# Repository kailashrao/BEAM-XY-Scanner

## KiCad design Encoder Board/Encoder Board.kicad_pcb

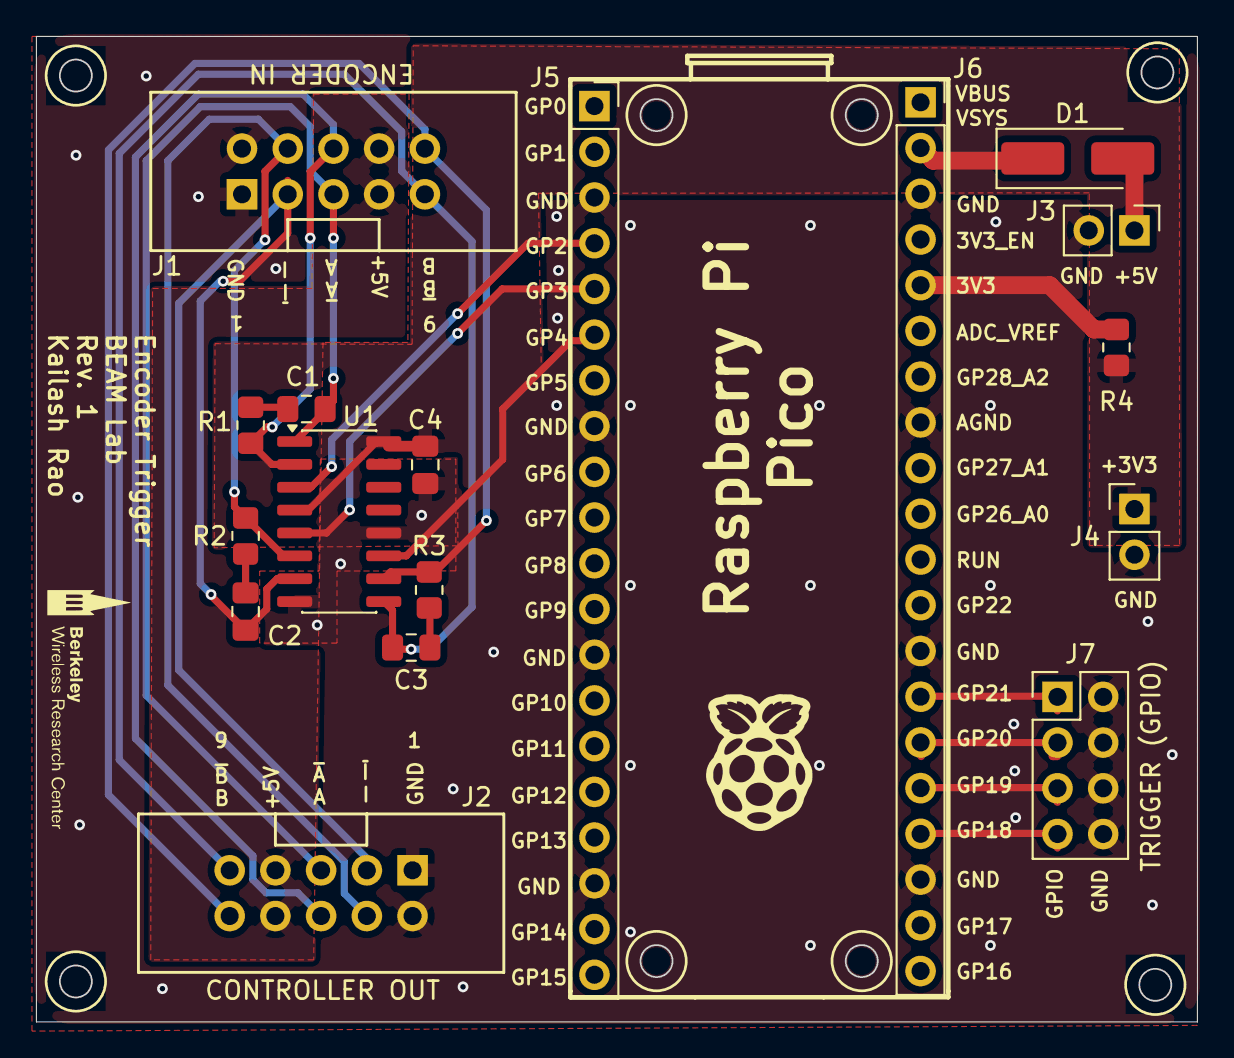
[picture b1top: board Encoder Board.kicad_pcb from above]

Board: 2 copper layers, 64.5 x 54.7 mm, 17 parts (0 on the bottom side), 22 nets.

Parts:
C1, C2, C3: 0.0047mF; C_0805_2012Metric_Pad1.18x1.45mm_HandSolder
C4: 0.1u; C_0805_2012Metric_Pad1.18x1.45mm_HandSolder
D1: D_Schottky; D_SMA_Handsoldering
J1, J2: Conn_02x05_Odd_Even; PinSocket_2x05_P2.54mm_Vertical_ClipConnector
J3, J4: Conn_01x02_Pin; PinHeader_1x02_P2.54mm_Vertical
J5, J6: Conn_01x20; PinSocket_1x20_P2.54mm_Vertical
J7: Conn_02x04_Odd_Even; PinHeader_2x04_P2.54mm_Vertical
R1, R2, R3: 110; R_0805_2012Metric_Pad1.20x1.40mm_HandSolder
R4: 0; R_0805_2012Metric_Pad1.20x1.40mm_HandSolder
U1: AM26LV32xD; SOIC-16_3.9x9.9mm_P1.27mm

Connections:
+3V3: C4.1, J4.1, R4.2, U1.4 (G), U1.16 (VDD)
+3V3_Pi: J6.5, R4.1
+5V_E: J1.7, J1.8, J2.7, J2.8
+5V_S: D1.2 (A), J3.1
/A: J1.6, J2.6, R1.2, U1.2 (1A)
/A_3V3: J5.4, U1.3 (1Y)
/A_N: C1.1, J1.5, J2.5, U1.1 (1B)
/B: J1.10, J2.10, R3.2, U1.10 (3A)
/B_3V3: J5.6, U1.11 (3Y)
/B_N: C3.1, J1.9, J2.9, U1.9 (3B)
/INDEX: J1.4, J2.4, R2.2, U1.6 (2A)
/INDEX_3V3: J5.5, U1.5 (2Y)
/INDEX_N: C2.1, J1.3, J2.3, U1.7 (2B)
/TRIGGER: J6.14, J7.1
GND: C4.2, J1.1, J1.2, J2.1, J2.2, J3.2, J4.2, J5.3, J5.8, J5.13, J5.18, J6.3, J6.8, J6.13, J6.18, J7.2, J7.4, J7.6, J7.8, U1.8 (GND), U1.12 (~G)
unnamed: C1.2, R1.1
unnamed: C2.2, R2.1
unnamed: C3.2, R3.1
unnamed: D1.1 (K), J6.2
unnamed: J6.15, J7.3
unnamed: J6.16, J7.5
unnamed: J6.17, J7.7

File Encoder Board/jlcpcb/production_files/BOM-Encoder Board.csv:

Comment,Designator,Footprint,LCSC,Quantity
0,R4,R_0805_2012Metric_Pad1.20x1.40mm_HandSolder,C844934,1
0.0047mF,"C1,C2,C3",C_0805_2012Metric_Pad1.18x1.45mm_HandSolder,C1746,3
0.1u,C4,C_0805_2012Metric_Pad1.18x1.45mm_HandSolder,C1711,1
110,"R1,R2,R3",R_0805_2012Metric_Pad1.20x1.40mm_HandSolder,C246031,3
AM26LV32xD,U1,SOIC-16_3.9x9.9mm_P1.27mm,C524786,1
Conn_01x02_Pin,"J3,J4",PinHeader_1x02_P2.54mm_Vertical,C32713268,2
Conn_01x20,"J5,J6",PinSocket_1x20_P2.54mm_Vertical,C7509519,2
Conn_02x04_Odd_Even,J7,PinHeader_2x04_P2.54mm_Vertical,C42431809,1
Conn_02x05_Odd_Even,"J1,J2",PinSocket_2x05_P2.54mm_Vertical_ClipConnector,C5665,2
D_Schottky,D1,D_SMA_Handsoldering,C83852,1

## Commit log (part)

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2026-05-17 testing latency with micropython native handlers
2026-05-18 Schematic w/differential receiver and line driver
2026-05-20 Layout
2026-05-20 Update 2x5 connector footprint
2026-05-20 Update diff pair terminating passives
2026-05-21 Update layout with new passives
2026-05-21 remove differential trigger
2026-05-21 Place & route components to optimize board size
2026-05-27 Update DRC from PCBWay
2026-05-28 Gerber files
2026-05-28 Add descriptive labels to silkscreen
2026-05-28 Fix J2 orientation
2026-05-28 Add orientation markers on silkscreen
2026-05-29 Updated gerber files
2026-05-30 change pico footprint, make extra GPIO pins available, re-route and place components, add power pours and stitching vias
2026-05-30 add BWRC logo, generate new gerbers
2026-05-30 updated gerber zip
2026-06-01 fix J1/J2 footprint
2026-06-01 dfm updates + gerbers
2026-06-01 new placement
2026-06-01 routing
2026-06-01 fix silkscreen
2026-06-02 fix J7 connections, C4/U1 decoupling cap connection
2026-06-02 implement .gitignore
2026-06-02 ignore .history/
2026-06-02 update gerbers
2026-06-02 Add more space for mounting holes
2026-06-04 final gerbers
2026-06-04 Further optimized scripts using viper and PIO
2026-06-04 update pico scripts documentation
2026-06-04 RC rise time + processing delay data and analysis scripts
2026-06-26 Update motor controller script names + plain otf meander scanning script
